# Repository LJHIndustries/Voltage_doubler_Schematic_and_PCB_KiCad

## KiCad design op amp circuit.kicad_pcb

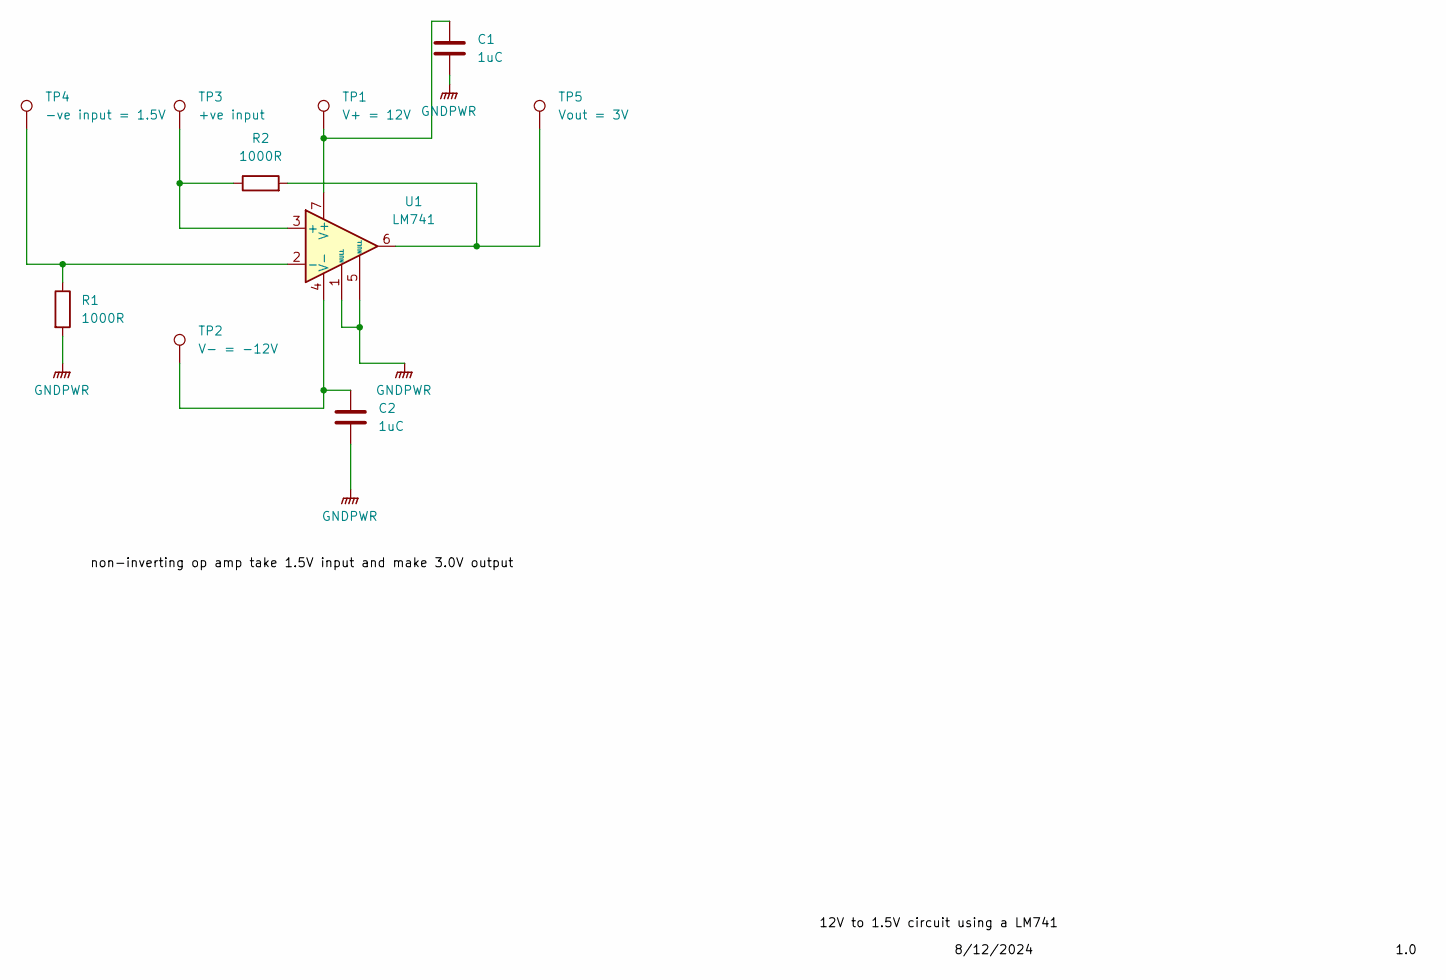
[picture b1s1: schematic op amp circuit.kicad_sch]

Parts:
C1, C2: 1uC; C_0603_1608Metric
R1, R2: 1000R; R_0603_1608Metric
TP1: V+ = 12V; TestPoint_Loop_D1.80mm_Drill1.0mm_Beaded
TP2: V- = -12V; TestPoint_Loop_D1.80mm_Drill1.0mm_Beaded
TP3: +ve input; TestPoint_Loop_D1.80mm_Drill1.0mm_Beaded
TP4: -ve input = 1.5V; TestPoint_Loop_D1.80mm_Drill1.0mm_Beaded
TP5: Vout = 3V; TestPoint_Loop_D1.80mm_Drill1.0mm_Beaded
U1: LM741; SOIC-8-1EP_3.9x4.9mm_P1.27mm_EP2.29x3mm

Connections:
GNDPWR: C1.2, C2.2, R1.2, U1.1 (NULL), U1.5 (NULL)
unnamed: R2.2, TP5.1, U1.6
unnamed: R2.1, TP3.1, U1.3 (+)
unnamed: R1.1, TP4.1, U1.2 (-)
unnamed: C1.1, TP1.1, U1.7 (V+)
unnamed: C2.1, TP2.1, U1.4 (V-)

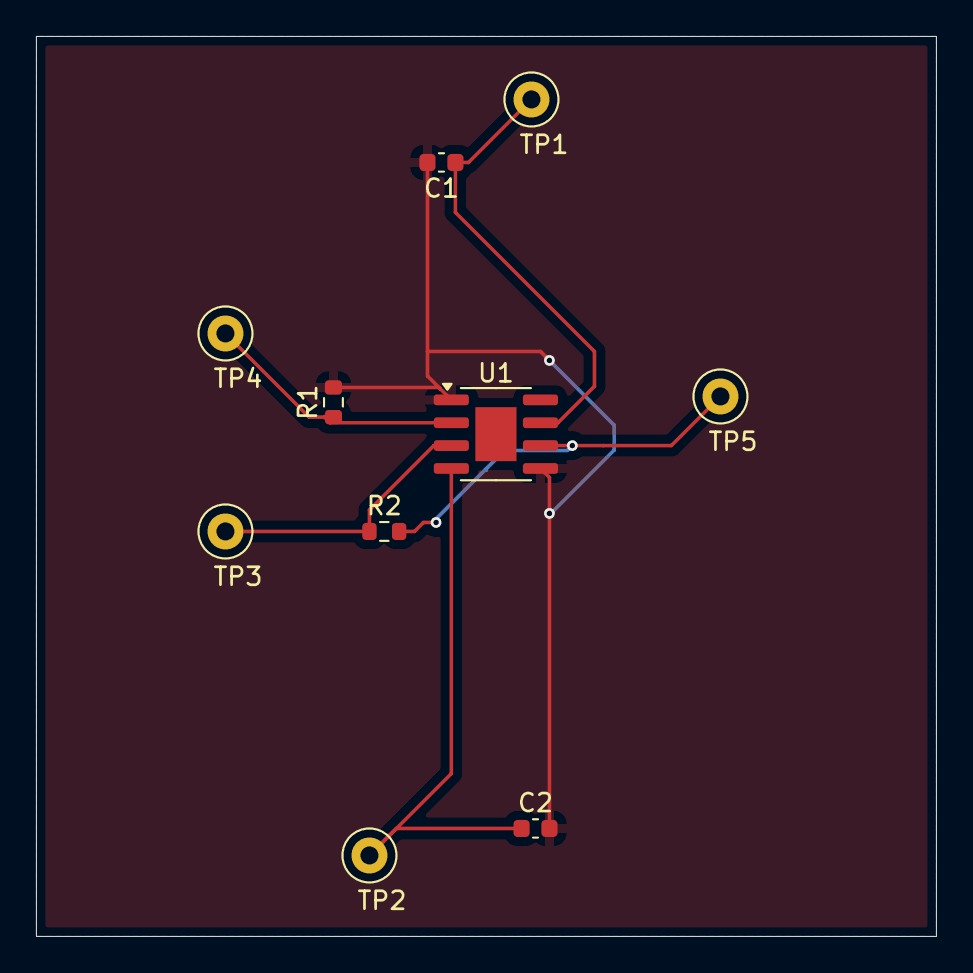
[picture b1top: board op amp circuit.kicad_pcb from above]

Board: 2 copper layers, 50.0 x 50.0 mm, 10 parts (0 on the bottom side), 6 nets.

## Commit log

2024-08-23 Add files via upload
    schematic, pcb layout, gerber and drill files, created using KiCad 8.0
